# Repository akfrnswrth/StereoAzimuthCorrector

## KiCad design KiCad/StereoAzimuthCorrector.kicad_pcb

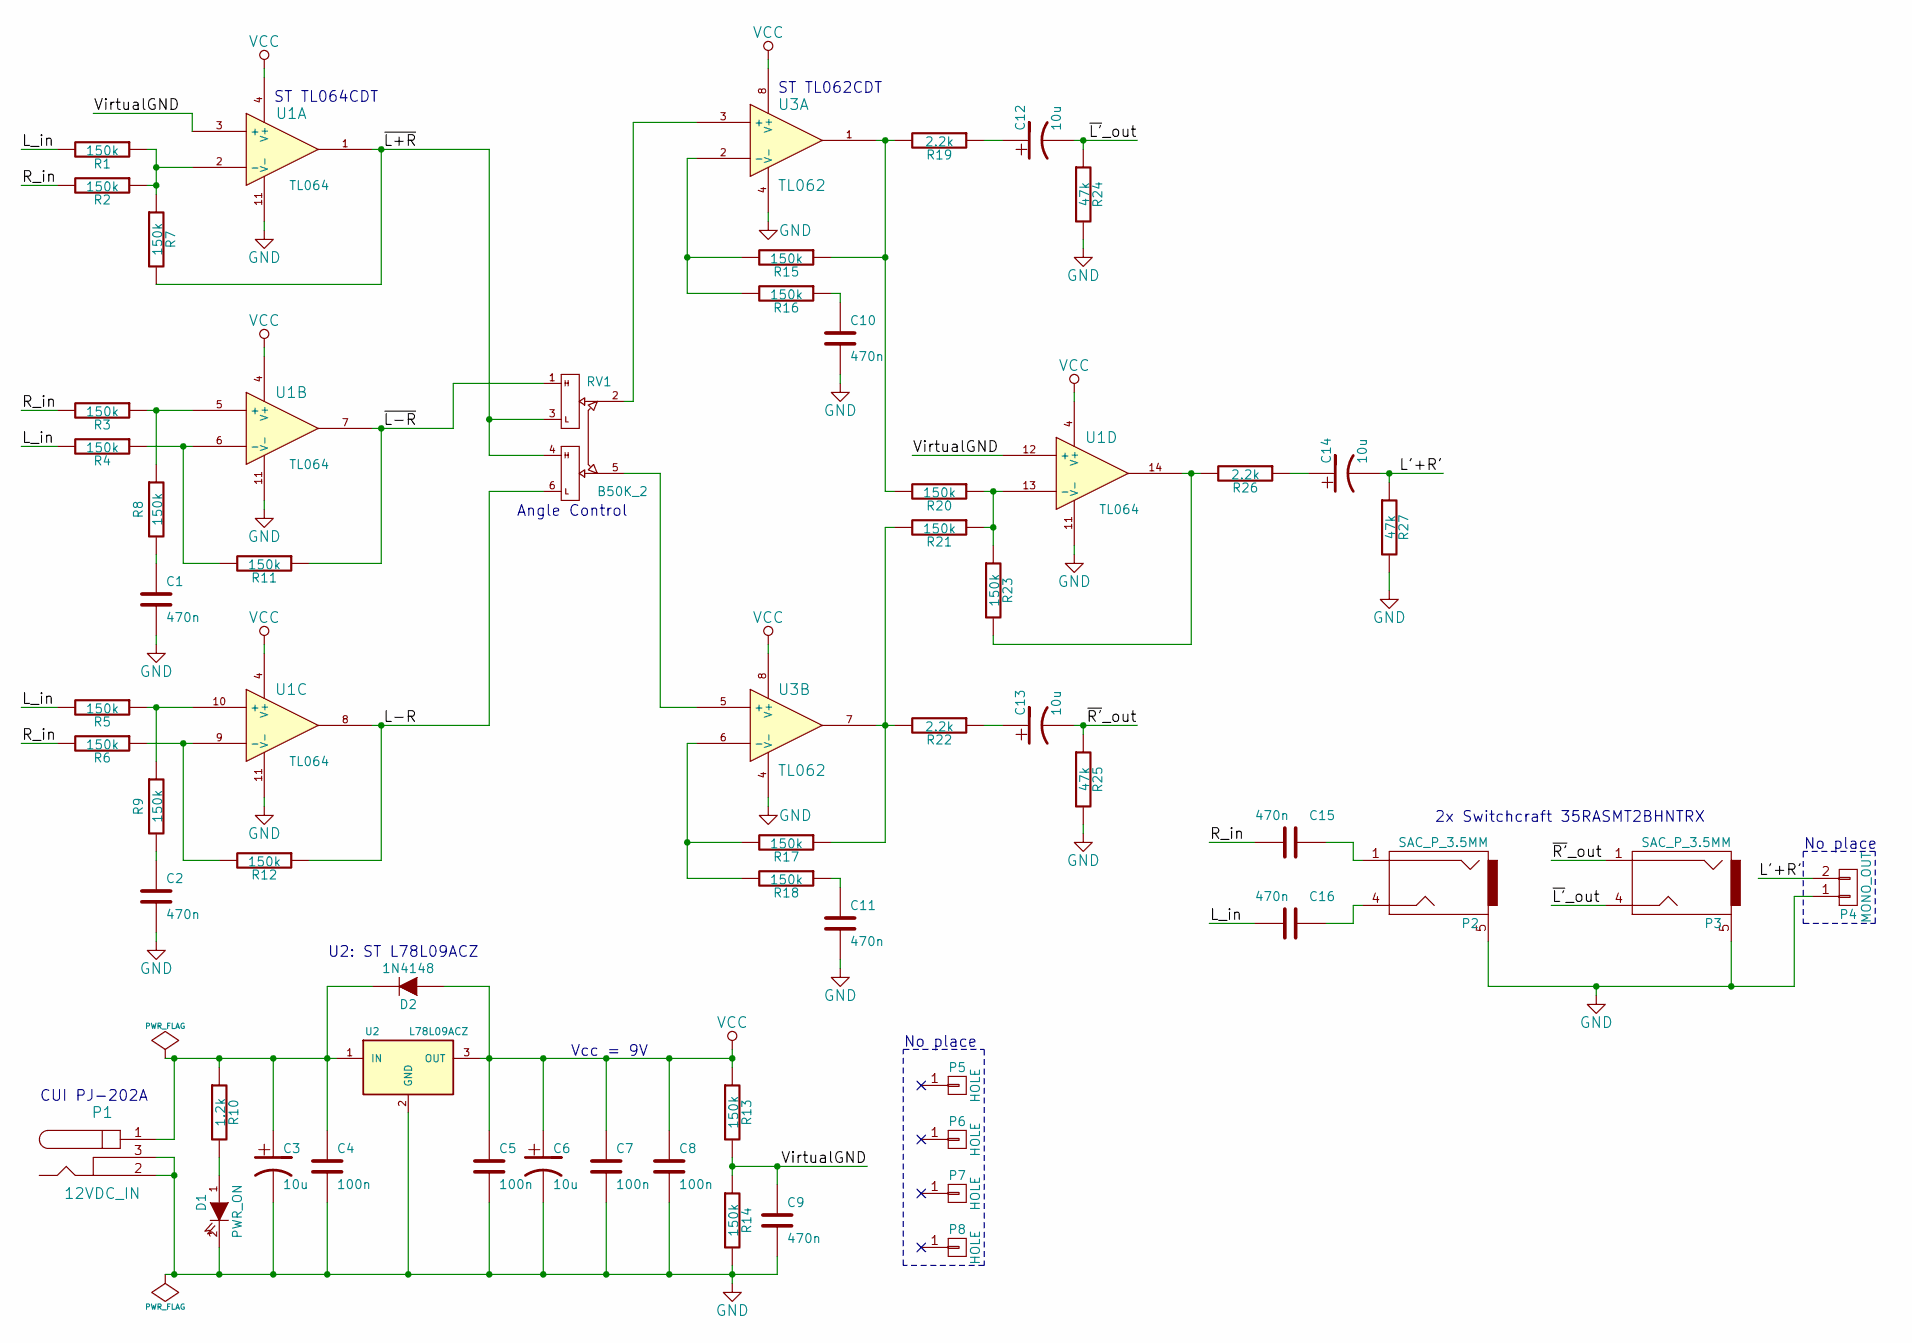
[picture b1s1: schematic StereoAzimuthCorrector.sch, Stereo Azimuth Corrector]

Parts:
C1, C2, C9, C10, C11, C15, C16: 470n; C_1206_HandSoldering
C3, C6, C12, C13, C14: 10u; Elko_vert_11x5mm_RM2
C4, C5, C7, C8: 100n; C_1206_HandSoldering
D1: PWR_ON; SAC_LED-5MM
D2: 1N4148; SAC_DO-35
P1: 12VDC_IN; BARREL_JACK
P2, P3: SAC_P_3.5MM
P4: MONO_OUT; Pin_Header_Straight_1x02
P5, P6, P7, P8: HOLE; MountingHole_2-5mm
R1, R2, R3, R4, R5, R6, R7, R8, R9, R11, R12, R13, R14, R15, R16, R17, R18, R20, R21, R23: 150k; R_1206_HandSoldering
R10: 1.2k; R_1206_HandSoldering
R19, R22, R26: 2.2k; R_1206_HandSoldering
R24, R25, R27: 47k; R_1206_HandSoldering
RV1: B50K_2; SAC_RV1
U1: TL064; SOIC-14_3.9x8.7mm_Pitch1.27mm
U2: L78L09ACZ; TO-92_Molded_Narrow
U3: TL062; SOIJ-8_5.3x5.3mm_Pitch1.27mm

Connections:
/L'+R': C14.2, P4.2, R27.1
/L-R: R12.1, RV1.6, U1.8
/L_in: C16.2, R1.2, R4.2, R5.2
/R_in: C15.2, R2.2, R3.2, R6.2
/VirtualGND: C9.1, R13.2, R14.1, U1.3 (+), U1.12 (+)
/~L'~_out: C12.2, P3.4, R24.1
/~L+R: R7.2, RV1.3, RV1.4, U1.1
/~L-R: R11.1, RV1.1, U1.7
/~R'~_out: C13.2, P3.1, R25.1
GND: C1.2, C2.2, C3.2, C4.2, C5.2, C6.2, C7.2, C8.2, C9.2, C10.2, C11.2, D1.2 (K), P1.2, P1.3, P2.5, P3.5, P4.1, R14.2, R24.2, R25.2, R27.2, U1.11 (V-), U2.2 (GND), U3.4 (V-)
unnamed: C1.1, R8.2
unnamed: C2.1, R9.2
unnamed: C3.1, C4.1, D2.2 (K), P1.1, R10.1, U2.1 (IN)
unnamed: C10.1, R16.1
unnamed: C11.1, R18.1
unnamed: C12.1, R19.1
unnamed: C13.1, R22.1
unnamed: C14.1, R26.1
unnamed: C15.1, P2.1
unnamed: C16.1, P2.4
unnamed: D1.1 (A), R10.2
unnamed: R1.1, R2.1, R7.1, U1.2 (-)
unnamed: R3.1, R8.1, U1.5 (+)
unnamed: R5.1, R9.1, U1.10 (+)
unnamed: R4.1, R11.2, U1.6 (-)
unnamed: R6.1, R12.2, U1.9 (-)
unnamed: R15.1, R19.2, R20.2, U3.1
unnamed: R15.2, R16.2, U3.2 (-)
unnamed: R17.1, R21.2, R22.2, U3.7
unnamed: R17.2, R18.2, U3.6 (-)
unnamed: R20.1, R21.1, R23.1, U1.13 (-)
unnamed: R23.2, R26.2, U1.14
unnamed: RV1.2, U3.3 (+)
unnamed: RV1.5, U3.5 (+)
VCC: C5.1, C6.1, C7.1, C8.1, D2.1 (A), R13.1, U1.4 (V+), U2.3 (OUT), U3.8 (V+)

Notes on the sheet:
Angle Control
Vcc = 9V
CUI PJ-202A
ST TL064CDT
ST TL062CDT
U2: ST L78L09ACZ
No place
2x Switchcraft 35RASMT2BHNTRX

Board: 2 copper layers, 57 parts (0 on the bottom side), 35 nets, no tracks yet.

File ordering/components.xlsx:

| Assembly Info |  |  |  |  |  | Ordering Info
 | REF | VAL | Rating | FP/package | Cust P/N |  | Cust P/N | Quantity | Supplier | MFR | MFR P/N | Sup P/N
 | C1 | 470n | 30V X7R | SMD 1206 | SAC_C_470N |  | SAC_C_470N | 7 | Mouser | AVX | 12065C474JAT2A | 581-12065C474J
 | C2 | 470n | 30V X7R | SMD 1206 | SAC_C_470N |  | SAC_C_10U | 5 | Mouser | Nichicon | UVR1H100MDD1TD | 647-UVR1H100MDD1TD
 | C3 | 10u | 20V Al | PTH 2mm | SAC_C_10U |  | SAC_C_100N | 4 | Mouser | Vishay | VJ1206Y104JXBTW1BC | 77-VJ1206Y104JXBTBC
 | C4 | 100n | 30V X7R | SMD 1206 | SAC_C_100N |  | SAC_D1 | 1 | Mouser | Lumex | SLX-LX5093ID | 696-SLX-LX5093ID
 | C5 | 100n | 30V X7R | SMD 1206 | SAC_C_100N |  | SAC_D2 | 1 | Mouser | Rectron | 1N4148-T | 583-1N4148-T
 | C6 | 10u | 20V Al | PTH 2mm | SAC_C_10U |  | SAC_P1 | 1 | Mouser | CUI | PJ-202A | 490-PJ-202A
 | C7 | 100n | 30V X7R | SMD 1206 | SAC_C_100N |  | SAC_P_3.5MM | 2 | Mouser | Switchcraft | 35RASMT2BHNTRX | 502-35RASMT2BHNTRX
 | C8 | 100n | 30V X7R | SMD 1206 | SAC_C_100N |  | SAC_R_150K | 20 | Mouser | Panasonic | ERJ-8ENF1503V | 667-ERJ-8ENF1503V
 | C9 | 470n | 30V X7R | SMD 1206 | SAC_C_470N |  | SAC_R_1.2K | 1 | Mouser | Panasonic | ERJ-8ENF1201V | 667-ERJ-8ENF1201V
 | C10 | 470n | 30V X7R | SMD 1206 | SAC_C_470N |  | SAC_R_2.2K | 3 | Mouser | Panasonic | ERJ-8ENF2201V | 667-ERJ-8ENF2201V
 | C11 | 470n | 30V X7R | SMD 1206 | SAC_C_470N |  | SAC_R_47K | 3 | Mouser | Panasonic | ERJ-8ENF4702V | 667-ERJ-8ENF4702V
 | C12 | 10u | 20V Al | PTH 2mm | SAC_C_10U |  | SAC_RV1 | 1 | Mouser | BI/TT | P120KGE-Y30BR50K | 858-P120KGE-Y30BR50K
 | C13 | 10u | 20V Al | PTH 2mm | SAC_C_10U |  | SAC_U1 | 1 | Mouser | STMicro | TL064CDT | 511-TL064CDT
 | C14 | 10u | 20V Al | PTH 2mm | SAC_C_10U |  | SAC_U2 | 1 | Mouser | STMicro | L78L09ACZ-AP | 511-L78L09ACZ-AP
 | C15 | 470n | 30V X7R | SMD 1206 | SAC_C_470N |  | SAC_U3 | 1 | Mouser | STMicro | TL062CDT | 511-TL062CDT
 | C16 | 470n | 30V X7R | SMD 1206 | SAC_C_470N |  | SAC_PSU | 1 | Mouser | Phihong | PSM03A-120-R | 552-PSM03A-120-R
 | D1 | PWR_ON | LED 5 mm | PTH 0.1in | SAC_D1 |  | SAC_ENC | 1
 | D2 | 1N4148 | 100 mA | DO-35 | SAC_D2 |  | SAC_PCB | 1 | OSH Park
 | P1 | 12VDC_IN | Barrel 2.1mm | CUI PJ-202A | SAC_P1
 | P2 | LR_IN | Stereo 3.5mm | 35RASMT2BHNTRX | SAC_P_3.5MM
 | P3 | LR_OUT | Stereo 3.5mm | 35RASMT2BHNTRX | SAC_P_3.5MM
 | P4 | MONO_OUT | No place | PTH 0.1in | -
 | P5 | HOLE | No place | Drill 3mm | -
 | P6 | HOLE | No place | Drill 3mm | -
 | P7 | HOLE | No place | Drill 3mm | -
 | P8 | HOLE | No place | Drill 3mm | -
 | R1 | 150k | 1% 1/4 W | SMD 1206 | SAC_R_150K
 | R2 | 150k | 1% 1/4 W | SMD 1206 | SAC_R_150K
 | R3 | 150k | 1% 1/4 W | SMD 1206 | SAC_R_150K
 | R4 | 150k | 1% 1/4 W | SMD 1206 | SAC_R_150K
 | R5 | 150k | 1% 1/4 W | SMD 1206 | SAC_R_150K
 | R6 | 150k | 1% 1/4 W | SMD 1206 | SAC_R_150K
 | R7 | 150k | 1% 1/4 W | SMD 1206 | SAC_R_150K
 | R8 | 150k | 1% 1/4 W | SMD 1206 | SAC_R_150K
 | R9 | 150k | 1% 1/4 W | SMD 1206 | SAC_R_150K
 | R10 | 1.2k | 5% 1/4 W | SMD 1206 | SAC_R_1.2K
 | R11 | 150k | 1% 1/4 W | SMD 1206 | SAC_R_150K
 | R12 | 150k | 1% 1/4 W | SMD 1206 | SAC_R_150K
 | R13 | 150k | 1% 1/4 W | SMD 1206 | SAC_R_150K
 | R14 | 150k | 1% 1/4 W | SMD 1206 | SAC_R_150K
 | R15 | 150k | 1% 1/4 W | SMD 1206 | SAC_R_150K
 | R16 | 150k | 1% 1/4 W | SMD 1206 | SAC_R_150K
 | R17 | 150k | 1% 1/4 W | SMD 1206 | SAC_R_150K
 | R18 | 150k | 1% 1/4 W | SMD 1206 | SAC_R_150K
 | R19 | 2.2k | 1% 1/4 W | SMD 1206 | SAC_R_2.2K
 | R20 | 150k | 1% 1/4 W | SMD 1206 | SAC_R_150K
 | R21 | 150k | 1% 1/4 W | SMD 1206 | SAC_R_150K
 | R22 | 2.2k | 1% 1/4 W | SMD 1206 | SAC_R_2.2K
 | R23 | 150k | 1% 1/4 W | SMD 1206 | SAC_R_150K
 | R24 | 47k | 1% 1/4 W | SMD 1206 | SAC_R_47K
 | R25 | 47k | 1% 1/4 W | SMD 1206 | SAC_R_47K
 | R26 | 2.2k | 1% 1/4 W | SMD 1206 | SAC_R_2.2K
 | R27 | 47k | 1% 1/4 W | SMD 1206 | SAC_R_47K
 | RV1 | B50K_2 | Dual lin pot | TT P120KGE | SAC_RV1
 | U1 | TL064 | Quad Op-Amp | SO-14 | SAC_U1
 | U2 | L78L09 | LDO 9V TO-92 | TO-92 | SAC_U2
 | U3 | TL062 | Dual Op-Amp | SO-8 | SAC_U3
 | Add'l Parts
 | PSU | Phihong PSM03A-120-R
 | PCB | OSH Park
 | ENC | New Age S3A-303010

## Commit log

2015-07-07 :lollipop: Added .gitattributes
2015-07-07 Created project
2015-07-07 Switch to low-power op-amp design
2015-07-07 Finish main circuitry
    Power supply (boost converter) is still TODO
2015-07-08 Remove unnecessary sheet
2015-07-08 Finish power circuitry; begin sourcing parts
2015-07-08 Add part comments for ICs, diode, LED
2015-07-09 Finalize component choice, add datasheets
2015-07-09 Rough in component placement
    Power jack footprint is still TODO
